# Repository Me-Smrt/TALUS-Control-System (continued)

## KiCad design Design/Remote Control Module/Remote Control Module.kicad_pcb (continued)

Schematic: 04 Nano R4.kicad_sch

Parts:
C8: C 10nF; C_0603_1608Metric; MPN GRM188R71H103KA01D
J2: Analog; PinSocket_1x15_P2.54mm_Vertical; MPN SSW-115-01-S-S
J3: Digital; PinSocket_1x15_P2.54mm_Vertical; MPN SSW-115-01-S-S
R5, R6: R 100k; R_0603_1608Metric; MPN RC0603FR-07100KL

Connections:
/02 CAN/CAN_CS_N: J3.13; also elsewhere on the board
/02 CAN/CAN_INT_N: J3.5; also elsewhere on the board
/02 CAN/CAN_STBY: J3.9; also elsewhere on the board
/02 CAN/SPI_MISO: J3.15; also elsewhere on the board
/02 CAN/SPI_MOSI: J3.14; also elsewhere on the board
/02 CAN/SPI_SCK: J2.1; also elsewhere on the board
/03 Safety/LOCAL_SERVO_ENABLE: J3.10; also elsewhere on the board
/04 Nano R4/DEBUG_RX: J3.2; also elsewhere on the board
/04 Nano R4/DEBUG_TX: J3.1; also elsewhere on the board
/04 Nano R4/LOGIC_PWR_SENSE: C8.1, J2.11, R5.2, R6.1
/04 Nano R4/RCB_IDENTIFY_N: J3.6; also elsewhere on the board
/5V_LOGIC: R5.1; also elsewhere on the board
/A_PG: J2.4; also elsewhere on the board
/B_PG: J2.5; also elsewhere on the board
/C_PG: J2.6; also elsewhere on the board
/D_PG: J2.7; also elsewhere on the board
/GLOBAL_SERVO_ALLOW_OK: J3.11; also elsewhere on the board
/REMOTE_VBUS: J2.15; also elsewhere on the board
/SCL: J2.9; also elsewhere on the board
/SDA: J2.8; also elsewhere on the board
/STATUS_LED: J3.12; also elsewhere on the board
GND: C8.2, J2.14, J3.4, R6.2; also elsewhere on the board

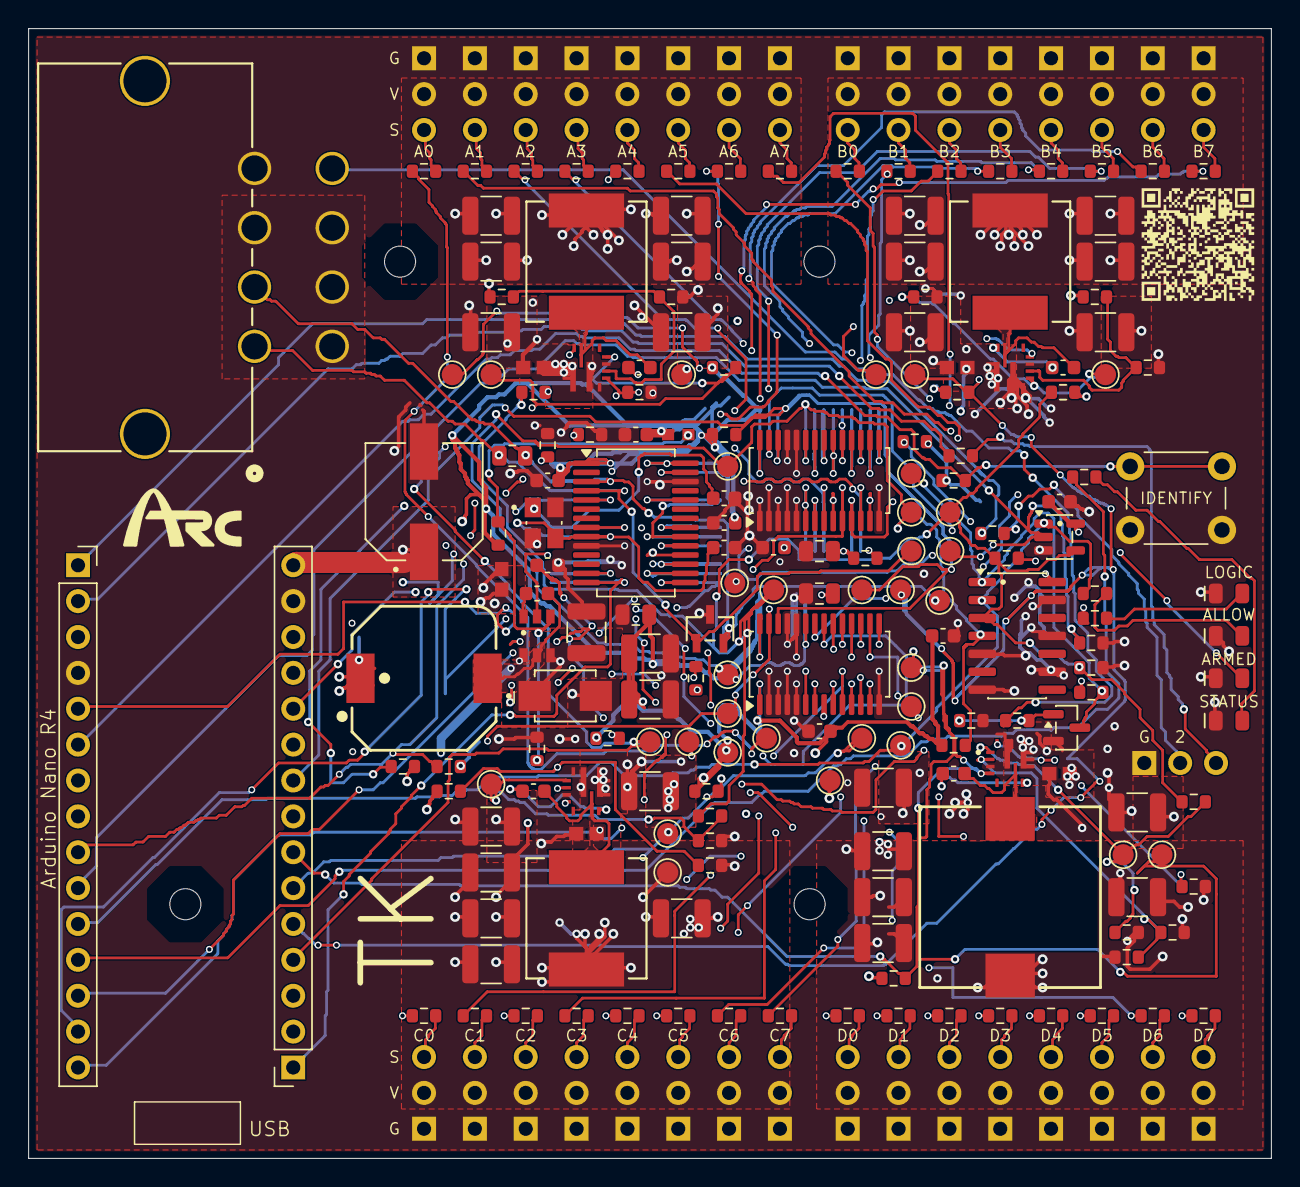
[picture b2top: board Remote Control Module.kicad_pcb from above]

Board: 4 copper layers, 88.0 x 80.0 mm, 227 parts (0 on the bottom side), 129 nets.

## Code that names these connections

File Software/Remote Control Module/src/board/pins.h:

#pragma once
#include <Arduino.h>

namespace automaton::pins {
constexpr uint8_t SPI_SCK_PIN = 13;
constexpr uint8_t SPI_MOSI_PIN = 11;
constexpr uint8_t SPI_MISO_PIN = 12;
constexpr uint8_t CAN_CS_N = 10;
constexpr uint8_t CAN_INT_N = 2;
constexpr uint8_t CAN_STBY = 6;

constexpr uint8_t LOCAL_SERVO_ENABLE = 7;
constexpr uint8_t GLOBAL_SERVO_ALLOW_OK = 8;
constexpr uint8_t RCB_IDENTIFY_N = 3;
constexpr uint8_t RCB_STATUS_LED = 9;

constexpr uint8_t BANK_A_PG = A0;
constexpr uint8_t BANK_B_PG = A1;
constexpr uint8_t BANK_C_PG = A2;
constexpr uint8_t BANK_D_PG = A3;
constexpr uint8_t I2C_SDA_PIN = A4;
constexpr uint8_t I2C_SCL_PIN = A5;
constexpr uint8_t LOGIC_PWR_SENSE = A7;

constexpr uint8_t DEBUG_TX = 1;
constexpr uint8_t DEBUG_RX = 0;
}

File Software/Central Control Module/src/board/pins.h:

#pragma once
#include <Arduino.h>

namespace automaton::ccb::pins {
// Nano R4 digital header mapping confirmed from the CCB PCB netlist.
constexpr uint8_t PI_HEARTBEAT = 2;          // D2 <- PI_HEARTBEAT_5V
constexpr uint8_t SUPERVISOR_ALLOW_REQ = 3; // D3 -> hardware E-stop/global-allow gate
constexpr uint8_t SUP_IO_INT_N = 6;          // D6 <- shared TCA9535/ADS7138 interrupt
constexpr uint8_t CCB_RGB_DATA = 7;          // D7 -> status RGB data
constexpr uint8_t PWR_FAULT_N = 8;           // D8 <- active-low CCB power fault
constexpr uint8_t PI_BUCK_PG = 9;            // D9 <- Pi 5 V buck power-good
constexpr uint8_t ESTOP_SENSE = 10;          // D10 <- LOW healthy, HIGH E-stop/open loop
constexpr uint8_t CCB_FAULT_LED = 11;         // D11 -> fault LED

constexpr uint8_t I2C_SDA_PIN = A4;
constexpr uint8_t I2C_SCL_PIN = A5;

// D0/D1 are used by Serial1 for Pi <-> Supervisor UART.
constexpr uint8_t SUP_UART_RX = 0;
constexpr uint8_t SUP_UART_TX = 1;
}
